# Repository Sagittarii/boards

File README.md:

boards
======

Printed board designs (using Eagle)

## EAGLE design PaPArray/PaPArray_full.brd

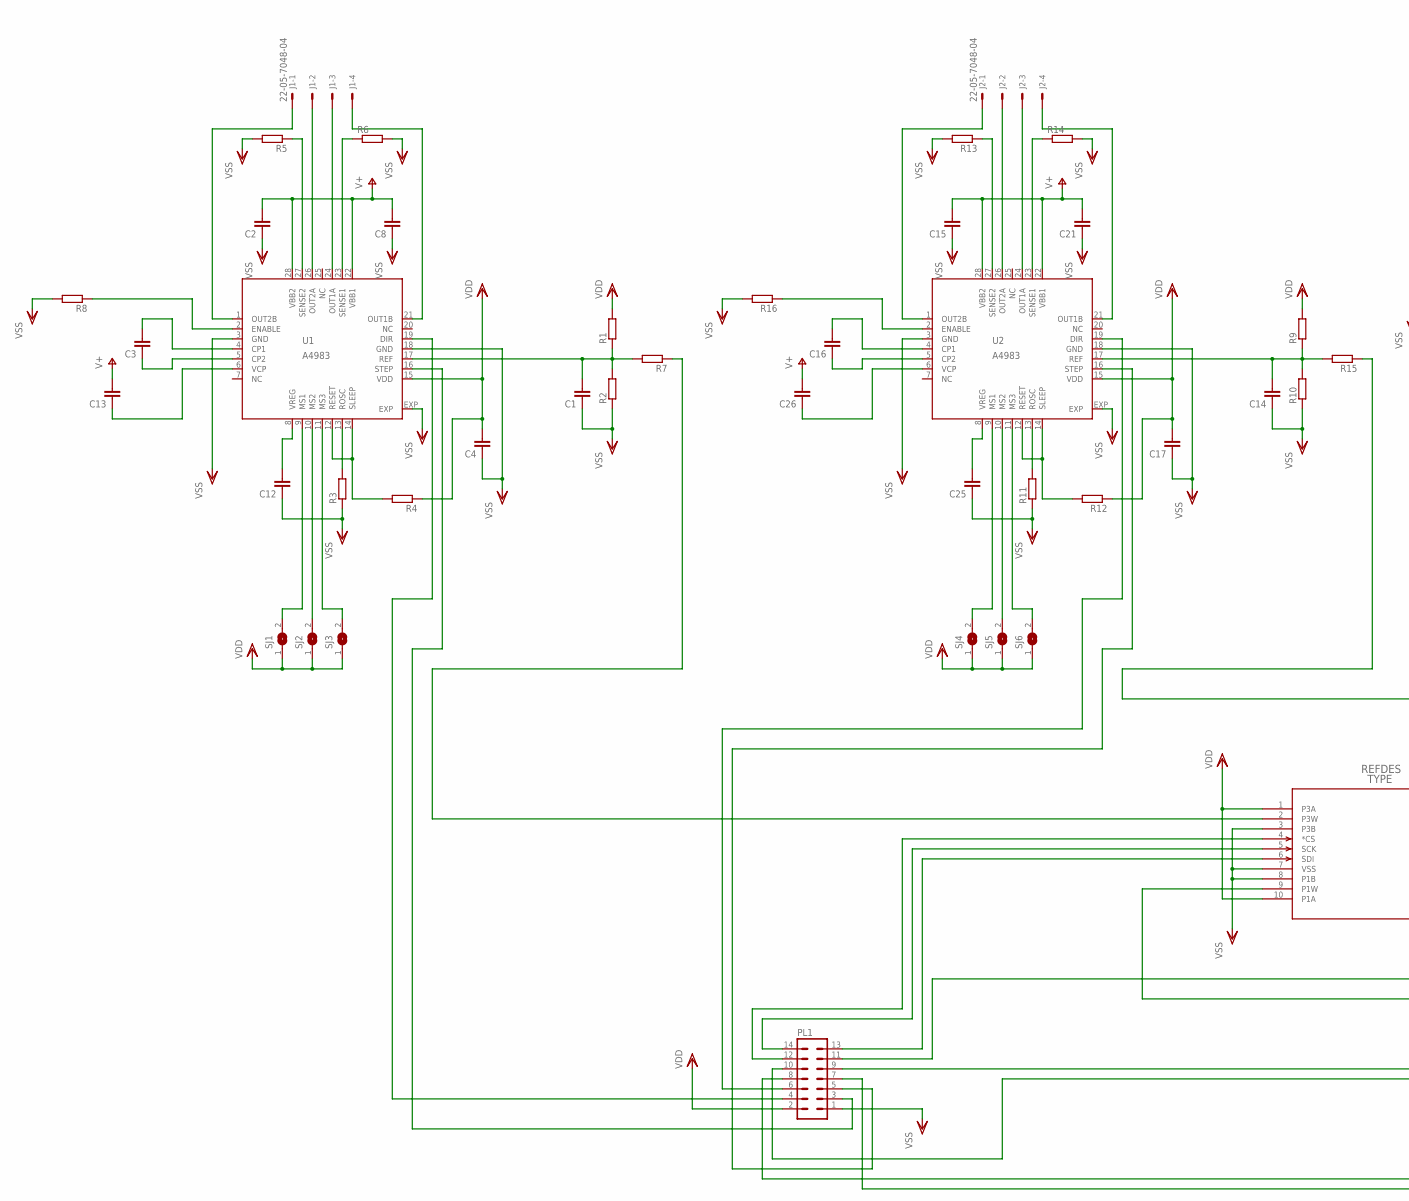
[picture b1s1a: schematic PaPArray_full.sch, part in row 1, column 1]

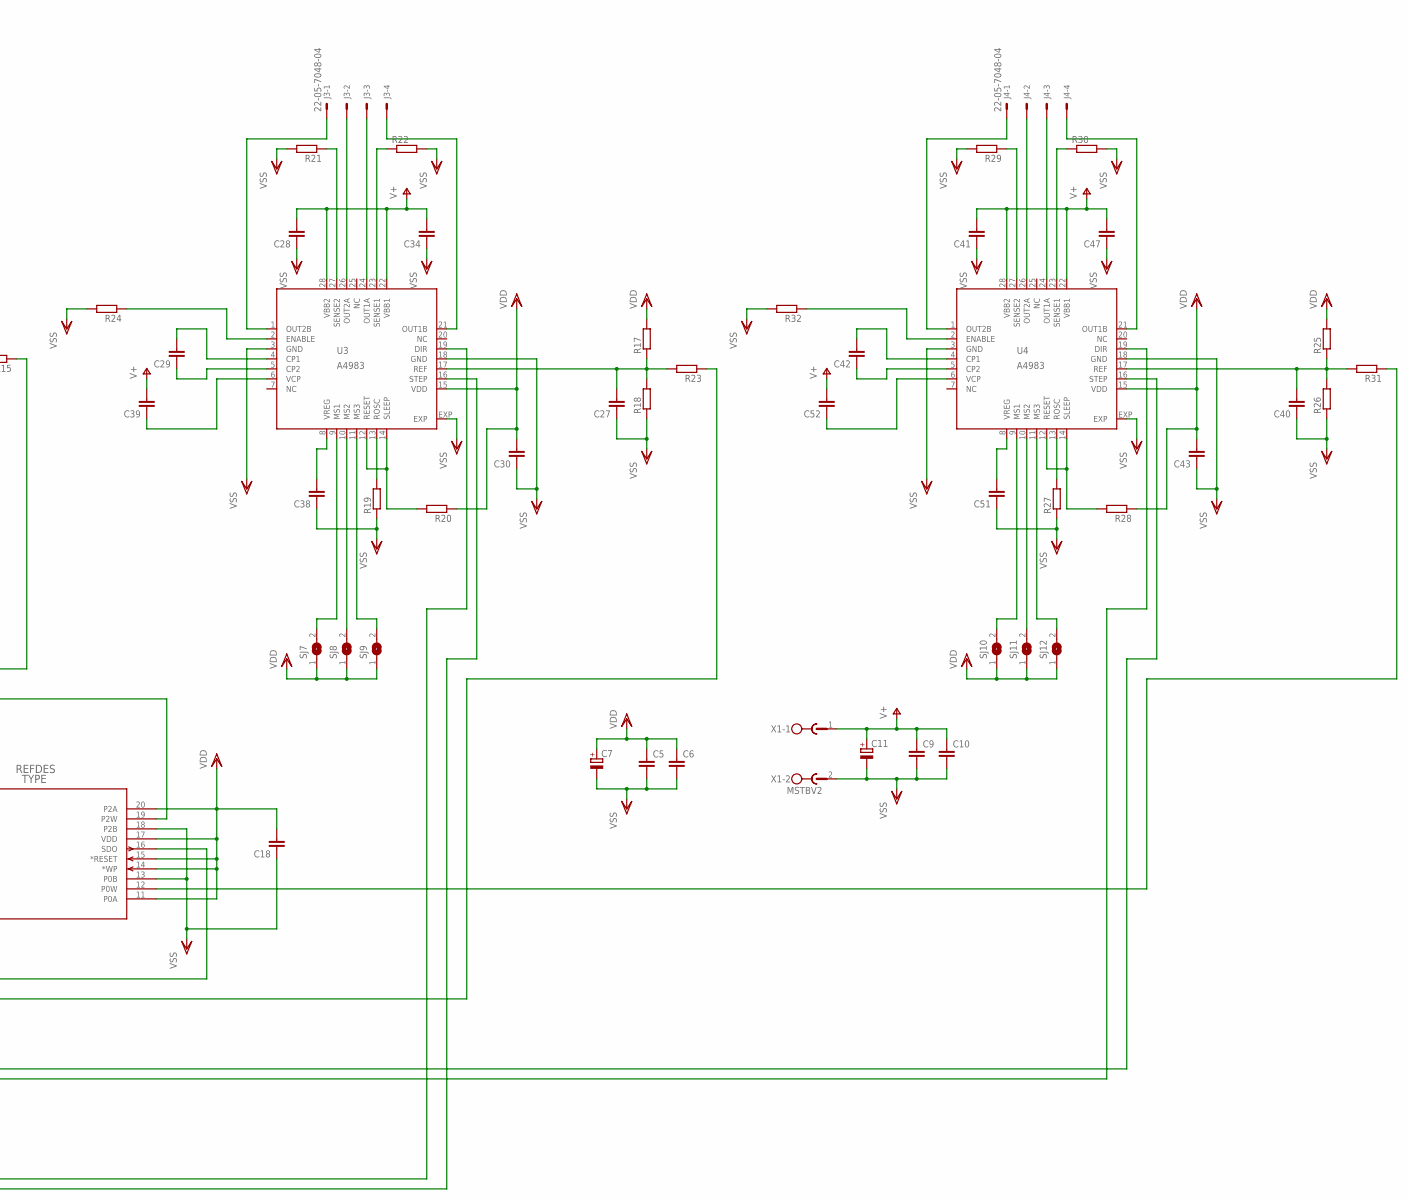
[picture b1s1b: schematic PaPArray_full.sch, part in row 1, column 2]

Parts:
C1, C2, C3, C4, C5, C6, C8, C9, C10, C12, C13, C14, C15, C16, C17, C18, C21, C25, C26, C27, C28, C29, C30, C34, C38, C39, C40, C41, C42, C43, C47, C51, C52: C-EUC0603; C0603
C7, C11: CPOL-EUE5-5; E5-5
J1, J2, J3, J4: 22-05-7048-04; 7395-04
PL1: 14V
R1, R2, R3, R4, R7, R8, R9, R10, R11, R12, R15, R16, R17, R18, R19, R20, R23, R24, R25, R26, R27, R28, R31, R32: R-EU_R0805; R0805
R5, R6, R13, R14, R21, R22, R29, R30: R-EU_R2512; R2512
SJ1, SJ2, SJ3, SJ4, SJ5, SJ6, SJ7, SJ8, SJ9, SJ10, SJ11, SJ12: SJ
U1, U2, U3, U4: A4983; QFN28ET
U$1: MCP4341-XXXX_ST; TSSOP20_MC
X1: MSTBV2

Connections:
unnamed: J1.3, U1.24 (OUT1A)
unnamed: J1.4, U1.21 (OUT1B)
unnamed: J1.2, U1.26 (OUT2A)
unnamed: J1.1, U1.1 (OUT2B)
unnamed: R5.1, U1.27 (SENSE2)
unnamed: R6.1, U1.23 (SENSE1)
unnamed: R3.2, U1.13 (ROSC)
unnamed: C3.2, U1.4 (CP1)
unnamed: C3.1, U1.5 (CP2)
unnamed: C1.2, R1.1, R2.2, R7.2, U1.17 (REF)
unnamed: C12.2, U1.8 (VREG)
unnamed: R31.1, U$1.12 (P0W)
unnamed: R4.2, U1.12 (RESET), U1.14 (SLEEP)
unnamed: J2.3, U2.24 (OUT1A)
unnamed: J2.4, U2.21 (OUT1B)
unnamed: J2.2, U2.26 (OUT2A)
unnamed: J2.1, U2.1 (OUT2B)
unnamed: R13.1, U2.27 (SENSE2)
unnamed: SJ1.2, U1.9 (MS1)
unnamed: SJ2.2, U1.10 (MS2)
unnamed: SJ3.2, U1.11 (MS3)
unnamed: R7.1, U$1.2 (P3W)
unnamed: PL1.3, U1.16 (STEP)
unnamed: PL1.4, U1.19 (DIR)
unnamed: C13.1, U1.6 (VCP)
unnamed: R14.1, U2.23 (SENSE1)
unnamed: C14.2, R9.1, R10.2, R15.2, U2.17 (REF)
unnamed: C16.2, U2.4 (CP1)
unnamed: C16.1, U2.5 (CP2)
unnamed: R11.2, U2.13 (ROSC)
unnamed: C25.2, U2.8 (VREG)
unnamed: R12.2, U2.12 (RESET), U2.14 (SLEEP)
unnamed: SJ4.2, U2.9 (MS1)
unnamed: SJ5.2, U2.10 (MS2)
unnamed: SJ6.2, U2.11 (MS3)
unnamed: PL1.5, U2.16 (STEP)
unnamed: PL1.6, U2.19 (DIR)
unnamed: C26.1, U2.6 (VCP)
unnamed: PL1.12, U$1.4 (*CS)
unnamed: R15.1, U$1.19 (P2W)
unnamed: J3.3, U3.24 (OUT1A)
unnamed: J3.4, U3.21 (OUT1B)
unnamed: J3.2, U3.26 (OUT2A)
unnamed: J3.1, U3.1 (OUT2B)
unnamed: R21.1, U3.27 (SENSE2)
unnamed: R22.1, U3.23 (SENSE1)
unnamed: C27.2, R17.1, R18.2, R23.2, U3.17 (REF)
unnamed: C29.2, U3.4 (CP1)
unnamed: C29.1, U3.5 (CP2)
unnamed: R19.2, U3.13 (ROSC)
unnamed: C38.2, U3.8 (VREG)
unnamed: R20.2, U3.12 (RESET), U3.14 (SLEEP)
unnamed: SJ7.2, U3.9 (MS1)
unnamed: SJ8.2, U3.10 (MS2)
unnamed: SJ9.2, U3.11 (MS3)
unnamed: PL1.7, U3.16 (STEP)
unnamed: PL1.8, U3.19 (DIR)
unnamed: C39.1, U3.6 (VCP)
unnamed: R16.1, U2.2 (ENABLE)
unnamed: PL1.14, U$1.5 (SCK)
unnamed: J4.3, U4.24 (OUT1A)
unnamed: J4.4, U4.21 (OUT1B)
unnamed: J4.2, U4.26 (OUT2A)
unnamed: J4.1, U4.1 (OUT2B)
unnamed: R29.1, U4.27 (SENSE2)
unnamed: R30.1, U4.23 (SENSE1)
unnamed: C40.2, R25.1, R26.2, R31.2, U4.17 (REF)
unnamed: C42.2, U4.4 (CP1)
unnamed: C42.1, U4.5 (CP2)
unnamed: R27.2, U4.13 (ROSC)
unnamed: C51.2, U4.8 (VREG)
unnamed: R28.2, U4.12 (RESET), U4.14 (SLEEP)
unnamed: SJ10.2, U4.9 (MS1)
unnamed: SJ11.2, U4.10 (MS2)
unnamed: SJ12.2, U4.11 (MS3)
unnamed: PL1.9, U4.16 (STEP)
unnamed: C52.1, U4.6 (VCP)
unnamed: R23.1, U$1.9 (P1W)
unnamed: PL1.13, U$1.6 (SDI)
unnamed: PL1.11, U$1.16 (SDO)
unnamed: R32.1, U4.2 (ENABLE)
unnamed: R8.1, U1.2 (ENABLE)
unnamed: R24.1, U3.2 (ENABLE)
unnamed: PL1.10, U4.19 (DIR)
V+: C2.2, C8.2, C9.1, C10.1, C11.+, C13.2, C15.2, C21.2, C26.2, C28.2, C34.2, C39.2, C41.2, C47.2, C52.2, U1.22 (VBB1), U1.28 (VBB2), U2.22 (VBB1), U2.28 (VBB2), U3.22 (VBB1), U3.28 (VBB2), U4.22 (VBB1), U4.28 (VBB2), X1.1
VDD: C4.2, C5.1, C6.1, C7.+, C17.2, C18.2, C30.2, C43.2, PL1.2, R1.2, R4.1, R9.2, R12.1, R17.2, R20.1, R25.2, R28.1, SJ1.1, SJ2.1, SJ3.1, SJ4.1, SJ5.1, SJ6.1, SJ7.1, SJ8.1, SJ9.1, SJ10.1, SJ11.1, SJ12.1, U1.15 (VDD), U2.15 (VDD), U3.15 (VDD), U4.15 (VDD), U$1.1 (P3A), U$1.10 (P1A), U$1.11 (P0A), U$1.14 (*WP), U$1.15 (*RESET), U$1.17 (VDD), U$1.20 (P2A)
VSS: C1.1, C2.1, C4.1, C5.2, C6.2, C7.-, C8.1, C9.2, C10.2, C11.-, C12.1, C14.1, C15.1, C17.1, C18.1, C21.1, C25.1, C27.1, C28.1, C30.1, C34.1, C38.1, C40.1, C41.1, C43.1, C47.1, C51.1, PL1.1, R2.1, R3.1, R5.2, R6.2, R8.2, R10.1, R11.1, R13.2, R14.2, R16.2, R18.1, R19.1, R21.2, R22.2, R24.2, R26.1, R27.1, R29.2, R30.2, R32.2, U1.3 (GND), U1.18 (GND), U1.EXP, U2.3 (GND), U2.18 (GND), U2.EXP, U3.3 (GND), U3.18 (GND), U3.EXP, U4.3 (GND), U4.18 (GND), U4.EXP, U$1.3 (P3B), U$1.7 (VSS), U$1.8 (P1B), U$1.13 (P0B), U$1.18 (P2B), X1.2

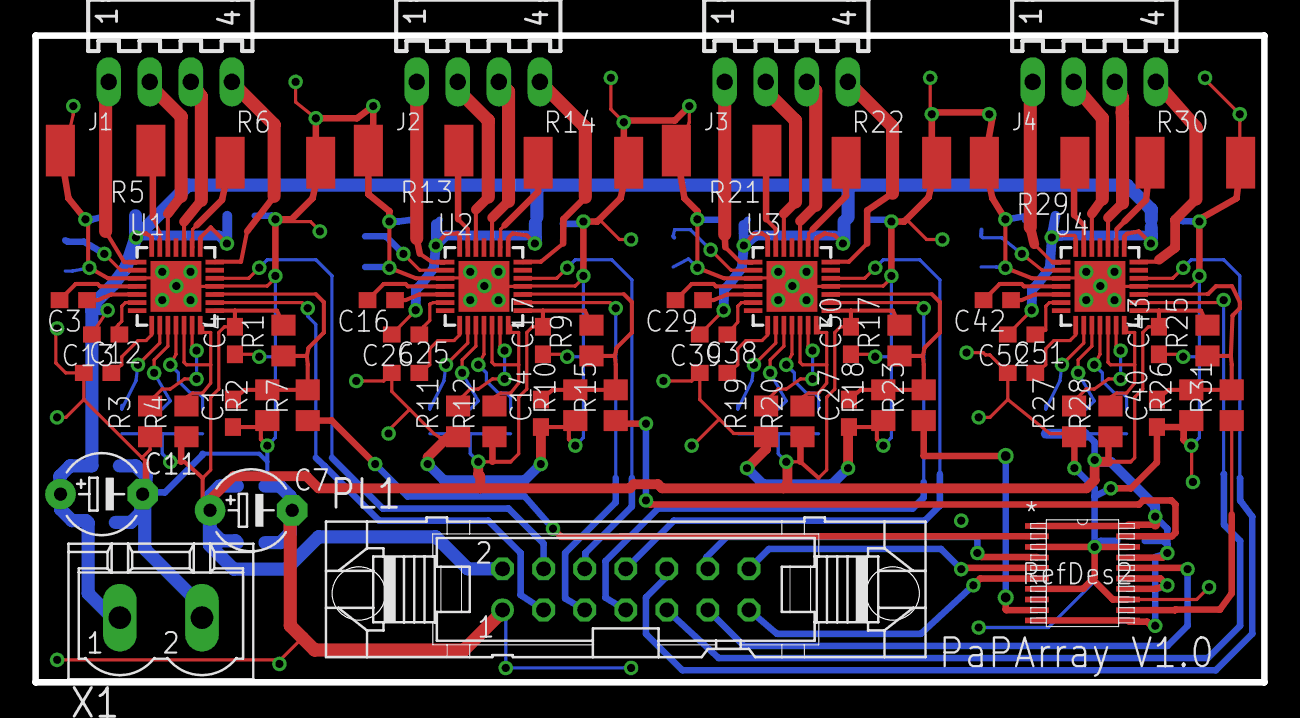
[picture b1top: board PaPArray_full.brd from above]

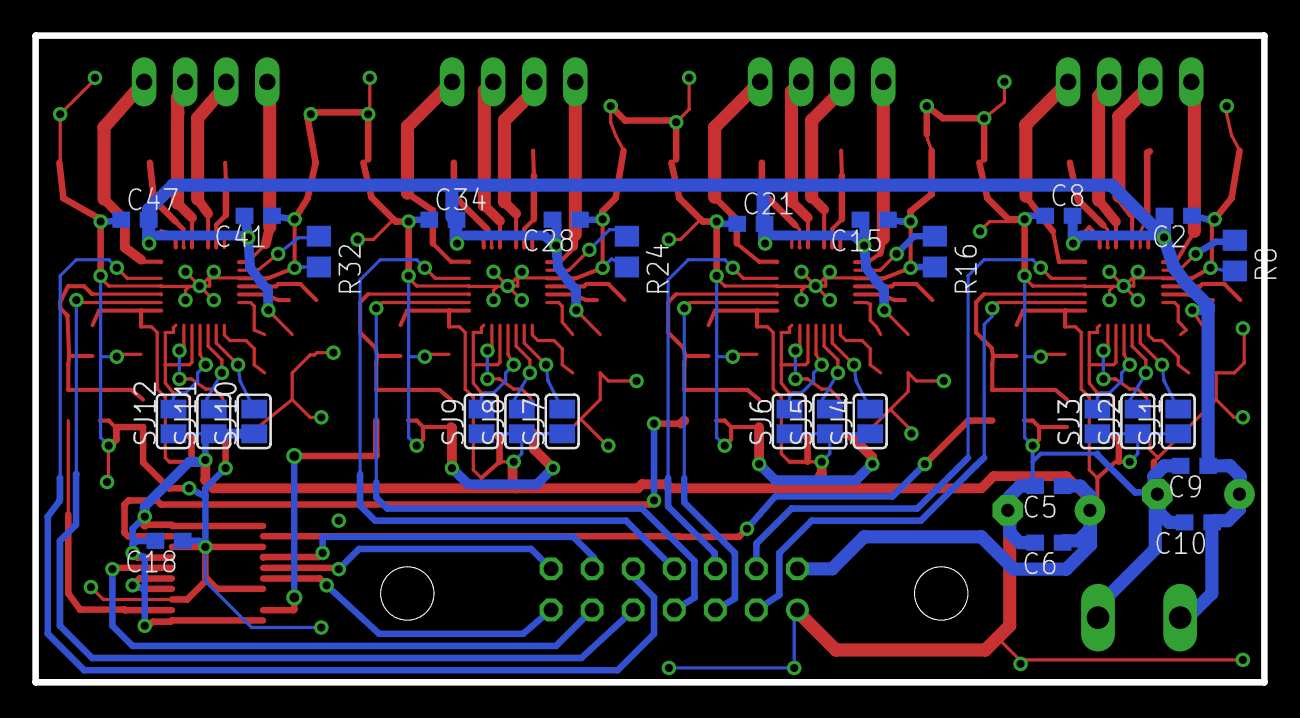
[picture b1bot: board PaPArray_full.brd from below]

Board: 2 copper layers, 76.0 x 40.0 mm, 90 parts (29 on the bottom side), 87 nets.

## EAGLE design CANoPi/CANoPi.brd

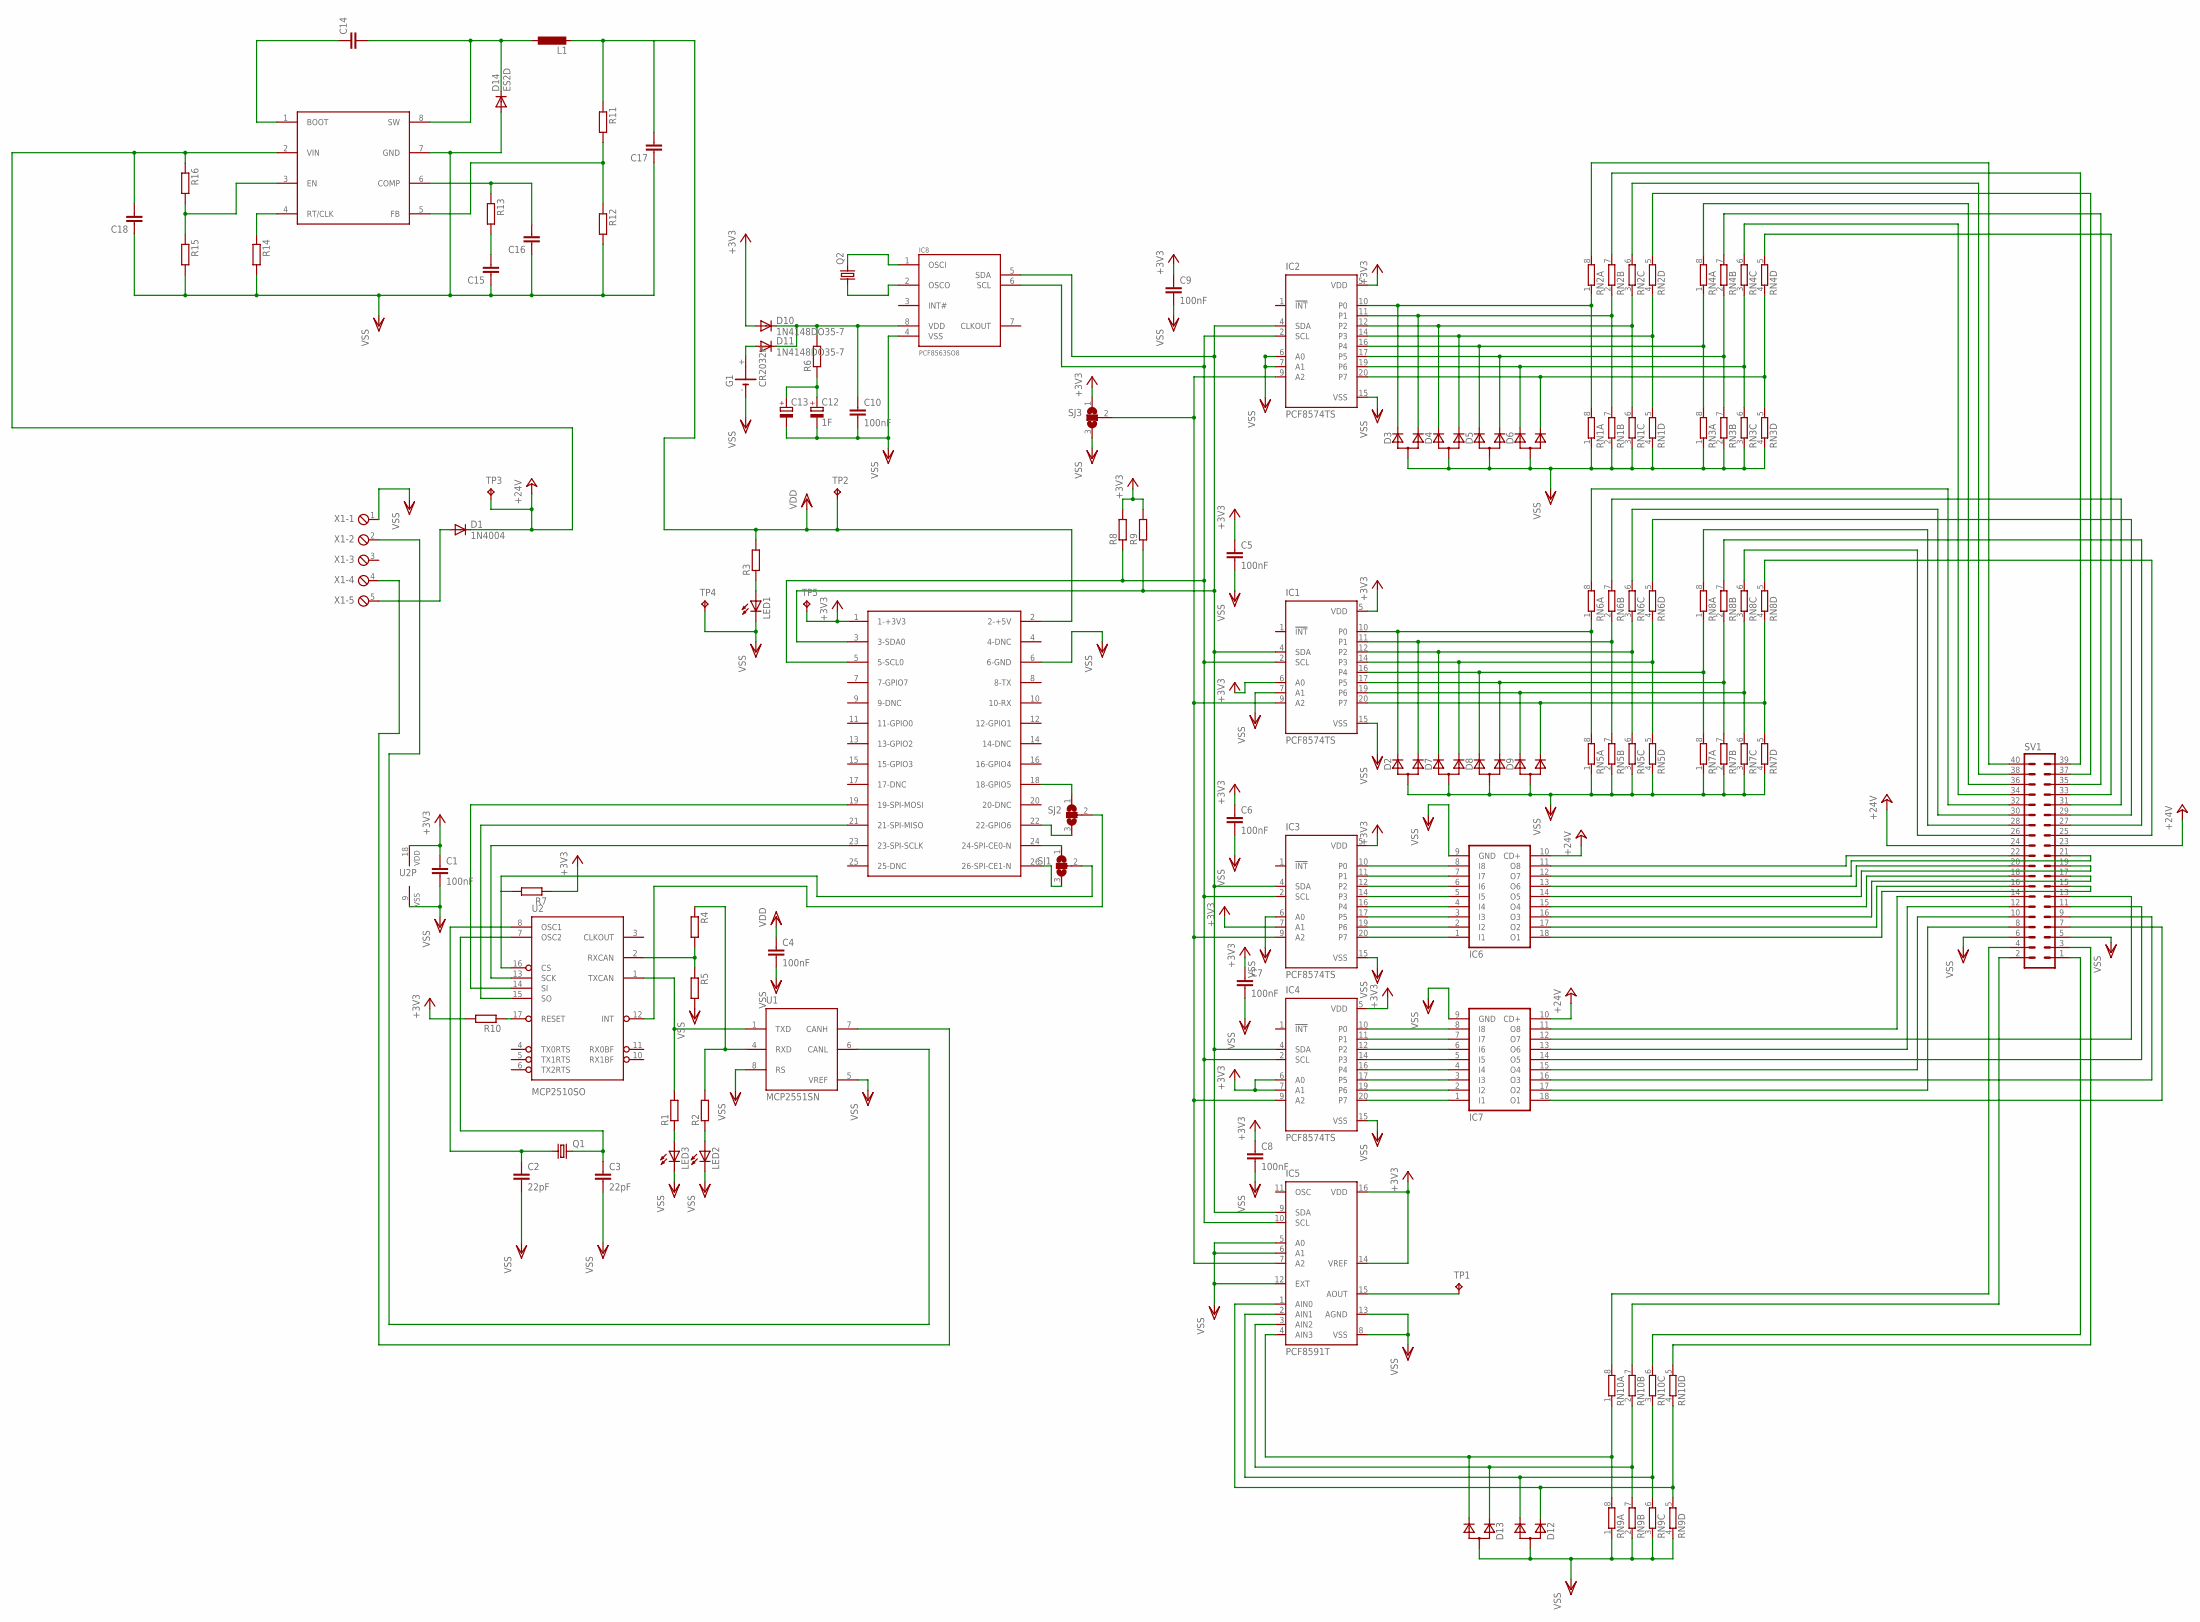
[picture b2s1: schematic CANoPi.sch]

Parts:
C1, C4, C5, C6, C7, C8, C9, C10: 100nF; C0603
C2, C3: 22pF; C1206
C12: 1F; CT3216
C13: CPOL-EUE5-6; E5-6
C14, C15, C16: C-EUC0805; C0805
C17, C18: C-EUC1210; C1210
D1: 1N4004; DO41-10
D2, D3, D4, D5, D6, D7, D8, D9, D12, D13: D_2CSOT23; SOT-23
D10, D11: 1N4148DO35-7; DO35-7
D14: ES2D; SMB
G1: CR2032H
IC1, IC2, IC3, IC4: PCF8574TS; SSOP20
IC5: PCF8591T; SO16W
IC6, IC7: ULN2804ASO18W; SO18W
IC8: PCF8563SO8; SOIC8
L1: L-EUWE-TPC; POWER-CHOKE_WE-TPC
LED1, LED2, LED3: LEDCHIPLED_1206; CHIPLED_1206
Q1, Q2: CRYSTALHC49S; HC49/S
R1, R2, R3, R4, R5, R6, R7, R8, R9, R10, R11, R12, R13, R14, R15, R16: R-EU_R0805; R0805
RN1, RN2, RN3, RN4, RN5, RN6, RN7, RN8, RN9, RN10: 4R-NEXBS8V; EXBS8V
SJ1, SJ2, SJ3: SJ2W; SJ_2
SV1: ML40L
TP1, TP2, TP3, TP4, TP5: TPPAD1-13; P1-13
U1: MCP2551SN; SO-08
U2: MCP2510SO; SO-18W
U$1: RASPBERRY-PI
U$2: TPS54340; SO-08
X1: MPT5; 5POL254

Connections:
+3V3: C1.1, C5.1, C6.1, C7.1, C8.1, C9.1, D10.A, IC1.5 (VDD), IC1.6 (A0), IC2.5 (VDD), IC3.5 (VDD), IC3.7 (A1), IC4.5 (VDD), IC4.6 (A0), IC4.7 (A1), IC5.14 (VREF), IC5.16 (VDD), R7.1, R8.2, R9.2, R10.2, SJ3.1, TP5.TP, U2.18 (VDD), U$1.1 (1-+3V3)
+24V: C18.2, D1.C, IC6.10 (CD+), IC7.10 (CD+), R16.1, SV1.23, SV1.24, TP3.TP, U$2.2 (VIN)
unnamed: R1.2, U1.1 (TXD), U2.1 (TXCAN)
unnamed: C2.1, Q1.1, U2.8 (OSC1)
unnamed: C3.1, Q1.2, U2.7 (OSC2)
unnamed: LED1.A, R3.1
unnamed: LED2.A, R2.1
unnamed: R2.2, R4.1, U1.4 (RXD)
unnamed: R4.2, R5.1, U2.2 (RXCAN)
unnamed: LED3.A, R1.1
unnamed: IC1.4 (SDA), IC2.4 (SDA), IC3.4 (SDA), IC4.4 (SDA), IC5.9 (SDA), IC8.5 (SDA), R9.1, U$1.3 (3-SDA0)
unnamed: IC1.2 (SCL), IC2.2 (SCL), IC3.2 (SCL), IC4.2 (SCL), IC5.10 (SCL), IC8.6 (SCL), R8.1, U$1.5 (5-SCL0)
unnamed: SJ2.2, U2.12 (INT)
unnamed: U2.15 (SO), U$1.21 (21-SPI-MISO)
unnamed: IC3.10 (P0), IC6.8 (I8)
unnamed: IC3.11 (P1), IC6.7 (I7)
unnamed: U2.14 (SI), U$1.19 (19-SPI-MOSI)
unnamed: U2.13 (SCK), U$1.23 (23-SPI-SCLK)
unnamed: R7.2, SJ1.2, U2.16 (CS)
unnamed: SJ2.3, U$1.22 (22-GPIO6)
unnamed: IC3.12 (P2), IC6.6 (I6)
unnamed: IC3.14 (P3), IC6.5 (I5)
unnamed: IC3.16 (P4), IC6.4 (I4)
unnamed: IC3.17 (P5), IC6.3 (I3)
unnamed: IC3.19 (P6), IC6.2 (I2)
unnamed: IC3.20 (P7), IC6.1 (I1)
unnamed: IC4.10 (P0), IC7.8 (I8)
unnamed: IC4.11 (P1), IC7.7 (I7)
unnamed: IC4.12 (P2), IC7.6 (I6)
unnamed: IC4.14 (P3), IC7.5 (I5)
unnamed: IC4.16 (P4), IC7.4 (I4)
unnamed: IC4.17 (P5), IC7.3 (I3)
unnamed: IC4.19 (P6), IC7.2 (I2)
unnamed: IC4.20 (P7), IC7.1 (I1)
unnamed: D1.A, X1.5
unnamed: U1.7 (CANH), X1.4
unnamed: U1.6 (CANL), X1.2
unnamed: RN4.7 (2), SV1.35
unnamed: RN4.5 (2), SV1.33
unnamed: RN4.6 (2), SV1.34
unnamed: D3.3 (C2), IC2.11 (P1), RN1.7 (2), RN2.2 (1)
unnamed: D4.2 (C1), IC2.12 (P2), RN1.6 (2), RN2.3 (1)
unnamed: D4.3 (C2), IC2.14 (P3), RN1.5 (2), RN2.4 (1)
unnamed: D5.2 (C1), IC2.16 (P4), RN3.8 (2), RN4.1
unnamed: RN4.8 (2), SV1.36
unnamed: D6.2 (C1), IC2.19 (P6), RN3.6 (2), RN4.3 (1)
unnamed: D6.3 (C2), IC2.20 (P7), RN3.5 (2), RN4.4 (1)
unnamed: D3.2 (C1), IC2.10 (P0), RN1.8 (2), RN2.1
unnamed: RN2.5 (2), SV1.37
unnamed: RN2.6 (2), SV1.38
unnamed: D5.3 (C2), IC2.17 (P5), RN3.7 (2), RN4.2 (1)
unnamed: RN2.7 (2), SV1.39
unnamed: IC6.11 (O8), SV1.22
unnamed: D2.3 (C2), IC1.11 (P1), RN5.7 (2), RN6.2 (1)
unnamed: D7.2 (C1), IC1.12 (P2), RN5.6 (2), RN6.3 (1)
unnamed: D7.3 (C2), IC1.14 (P3), RN5.5 (2), RN6.4 (1)
unnamed: D8.2 (C1), IC1.16 (P4), RN7.8 (2), RN8.1
unnamed: D9.2 (C1), IC1.19 (P6), RN7.6 (2), RN8.3 (1)
unnamed: D9.3 (C2), IC1.20 (P7), RN7.5 (2), RN8.4 (1)
unnamed: D2.2 (C1), IC1.10 (P0), RN5.8 (2), RN6.1
unnamed: D8.3 (C2), IC1.17 (P5), RN7.7 (2), RN8.2 (1)
unnamed: RN8.5 (2), SV1.25
unnamed: RN8.6 (2), SV1.26
unnamed: RN8.7 (2), SV1.27
unnamed: RN8.8 (2), SV1.28
unnamed: RN6.5 (2), SV1.29
unnamed: RN6.6 (2), SV1.30
unnamed: RN6.7 (2), SV1.31
unnamed: RN6.8 (2), SV1.32
unnamed: IC8.1 (OSCI), Q2.2
unnamed: IC8.2 (OSCO), Q2.1
unnamed: D11.A, G1.+
unnamed: C10.1, D10.C, D11.C, IC8.8 (VDD), R6.2
unnamed: C12.+, C13.+, R6.1
unnamed: IC5.15 (AOUT), TP1.TP
unnamed: D12.2 (C1), IC5.1 (AIN0), RN9.5 (2), RN10.4 (1)
unnamed: D12.3 (C2), IC5.2 (AIN1), RN9.6 (2), RN10.3 (1)
unnamed: IC1.9 (A2), IC2.9 (A2), IC3.9 (A2), IC4.9 (A2), IC5.7 (A2), SJ3.2
unnamed: D13.2 (C1), IC5.3 (AIN2), RN9.7 (2), RN10.2 (1)
unnamed: D13.3 (C2), IC5.4 (AIN3), RN9.8 (2), RN10.1
unnamed: SJ1.3, U$1.26 (26-SPI-CE1-N)
unnamed: SJ1.1, U$1.24 (24-SPI-CE0-N)
unnamed: SJ2.1, U$1.18 (18-GPIO5)
unnamed: IC6.12 (O7), SV1.21
unnamed: IC6.13 (O6), SV1.20
unnamed: RN10.5 (2), SV1.3
unnamed: RN10.6 (2), SV1.1
unnamed: RN10.7 (2), SV1.2
unnamed: RN10.8 (2), SV1.4
unnamed: IC6.14 (O5), SV1.19
unnamed: IC6.15 (O4), SV1.18
unnamed: IC6.16 (O3), SV1.17
unnamed: IC6.17 (O2), SV1.16
unnamed: IC6.18 (O1), SV1.15
unnamed: RN2.8 (2), SV1.40
unnamed: IC7.11 (O8), SV1.14
unnamed: IC7.12 (O7), SV1.13
unnamed: IC7.13 (O6), SV1.12
unnamed: IC7.14 (O5), SV1.11
unnamed: IC7.15 (O4), SV1.10
unnamed: IC7.16 (O3), SV1.9
unnamed: IC7.17 (O2), SV1.8
unnamed: IC7.18 (O1), SV1.7
unnamed: R10.1, U2.17 (RESET)
unnamed: R15.1, R16.2, U$2.3 (EN)
unnamed: R14.1, U$2.4 (RT/CLK)
unnamed: R11.2, R12.1, U$2.5 (FB)
unnamed: C16.2, R13.1, U$2.6 (COMP)
unnamed: C15.2, R13.2
unnamed: C14.1, U$2.1 (BOOT)
unnamed: C14.2, D14.C, L1.1, U$2.8 (SW)
VDD: C4.1, C17.2, L1.2, R3.2, R11.1, TP2.TP, U1.3 (VDD), U$1.2 (2-+5V)
VSS: C1.2, C2.2, C3.2, C4.2, C5.2, C6.2, C7.2, C8.2, C9.2, C10.2, C12.-, C13.-, C15.1, C16.1, C17.1, C18.1, D2.1 (A), D3.1 (A), D4.1 (A), D5.1 (A), D6.1 (A), D7.1 (A), D8.1 (A), D9.1 (A), D12.1 (A), D13.1 (A), D14.A, G1.-, IC1.7 (A1), IC1.15 (VSS), IC2.6 (A0), IC2.7 (A1), IC2.15 (VSS), IC3.6 (A0), IC3.15 (VSS), IC4.15 (VSS), IC5.5 (A0), IC5.6 (A1), IC5.8 (VSS), IC5.12 (EXT), IC5.13 (AGND), IC6.9 (GND), IC7.9 (GND), IC8.4 (VSS), LED1.C, LED2.C, LED3.C, R5.2, R12.2, R14.2, R15.2, RN1.1, RN1.2 (1), RN1.3 (1), RN1.4 (1), RN3.1, RN3.2 (1), RN3.3 (1), RN3.4 (1), RN5.1, RN5.2 (1), RN5.3 (1), RN5.4 (1), RN7.1, RN7.2 (1), RN7.3 (1), RN7.4 (1), RN9.1, RN9.2 (1), RN9.3 (1), RN9.4 (1), SJ3.3, SV1.5, SV1.6, TP4.TP, U1.2 (VSS), U1.5 (VREF), U1.8 (RS), U2.9 (VSS), U$1.6 (6-GND), U$2.7 (GND), X1.1

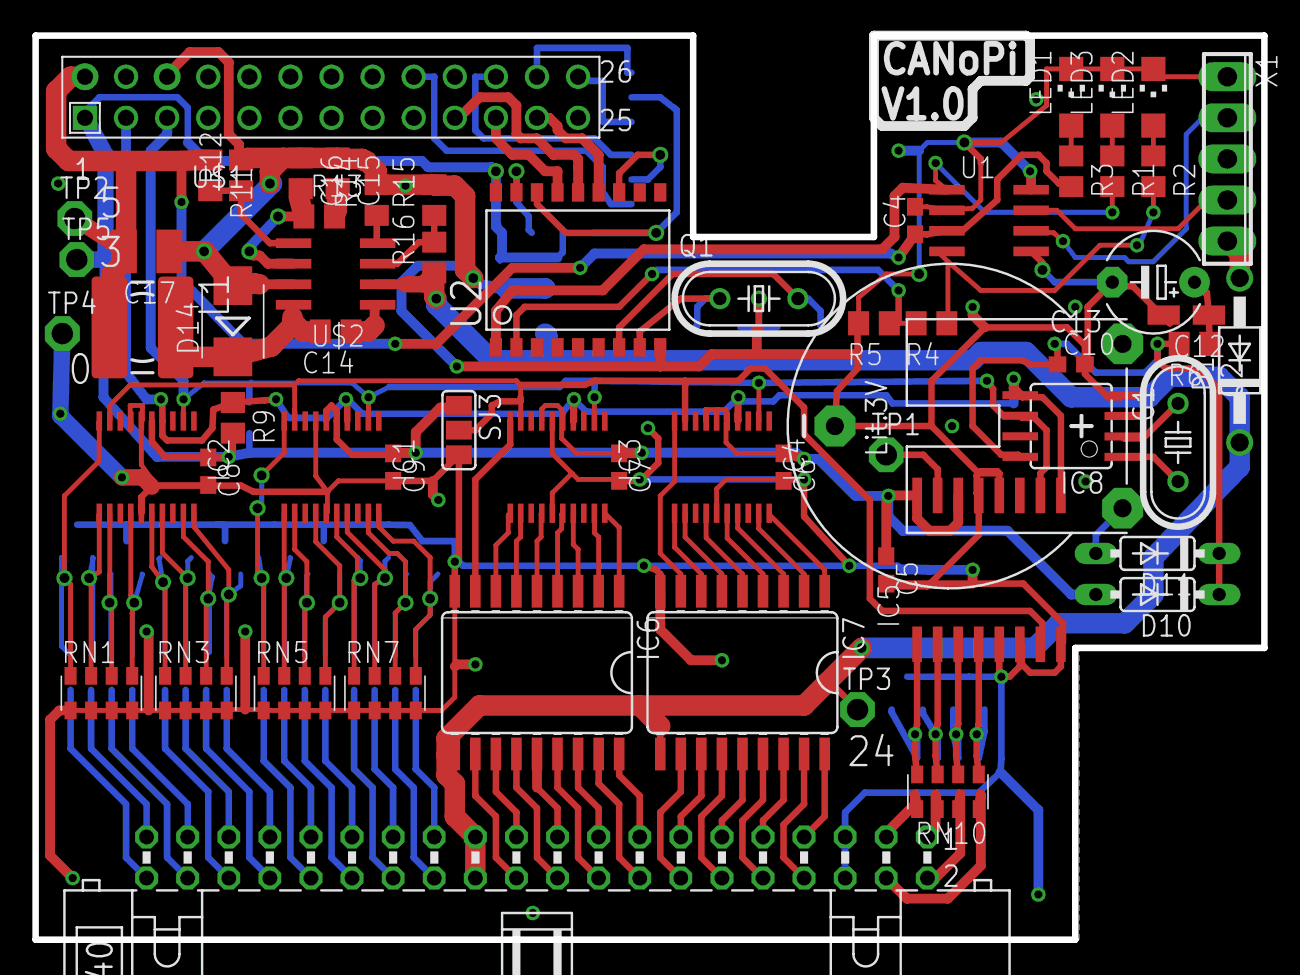
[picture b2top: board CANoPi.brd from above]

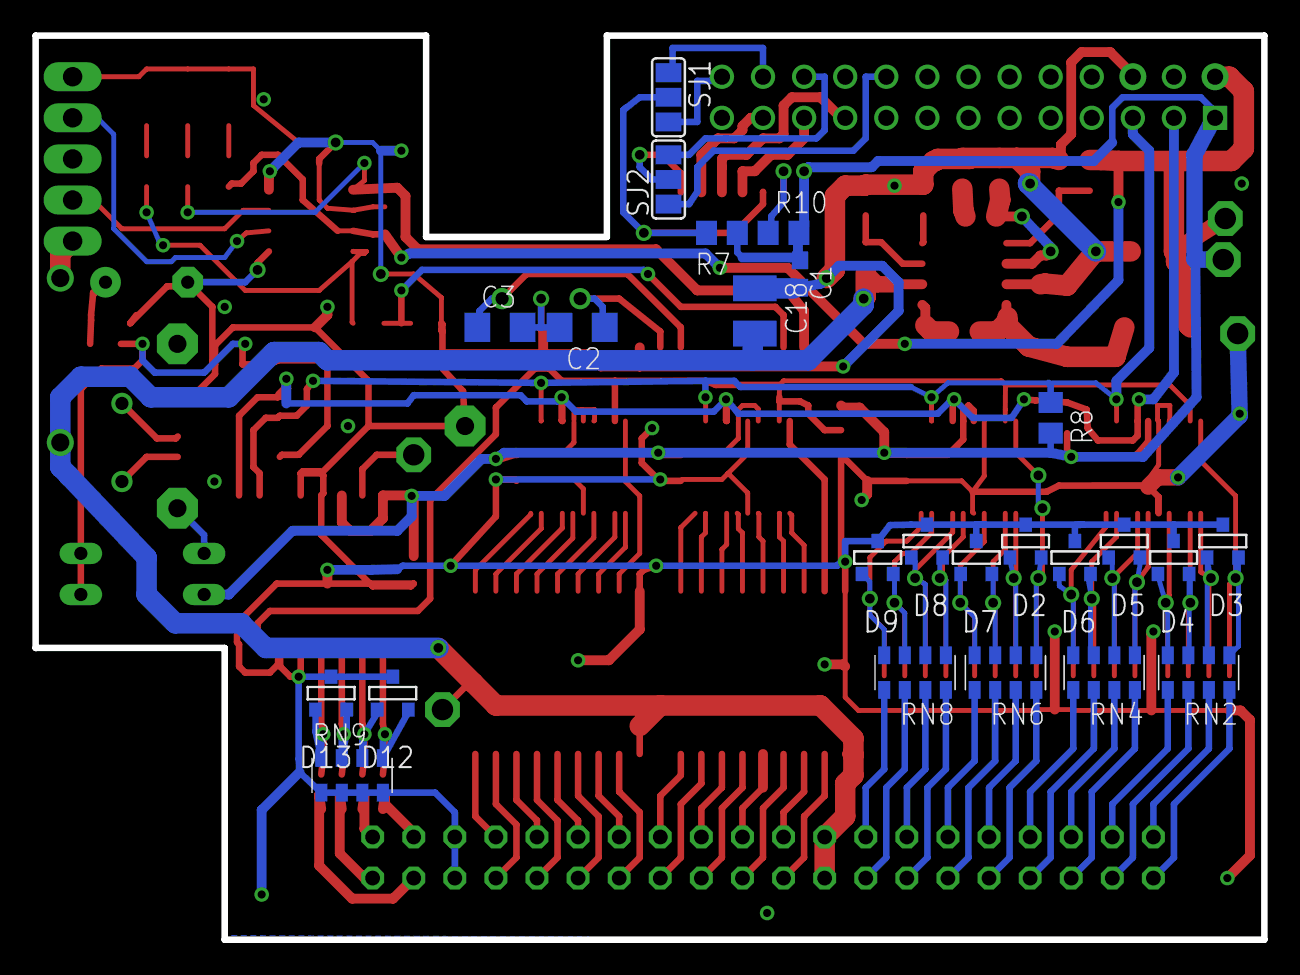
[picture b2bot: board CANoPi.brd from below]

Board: 2 copper layers, 75.9 x 55.9 mm, 86 parts (24 on the bottom side), 113 nets.

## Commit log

2013-03-24 Add CANoPi and PaPArray boards
